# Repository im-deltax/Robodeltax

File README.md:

# Robodeltax

An educational AI chatbot robot under development by [im-deltax](https://github.com/im-deltax).

This repository currently publishes robot design assets: editable 3D files, printable parts, electronics designs, and garment patterns. The main chatbot application and production firmware are not available yet. Learning assistance is the intended application, not a capability demonstrated by this release.

## Current assets

| Folder | Contents |
| --- | --- |
| `Blender/` | Current assembled Kimono scene, V21 |
| `Vo_In_3D/` | Printable STL parts and available editable CAD/STEP sources |
| `Trang_Phuc/` | Current V20 garment patterns, sewing documents, print artwork and textures |
| `Dien_Tu/` | KiCad sources, custom libraries, prototype manufacturing exports and assembly documents |
| `Nguon_CAD_Giu_Lai/` | Older CAD retained for reference; not the current printing set |
| Other outfit folders | Design variants and reference-based studies, including folders marked `BANSAO` (copies); these are not all current approved manufacturing sets |

Read **[MO_FILE_NAY_TRUOC.txt](MO_FILE_NAY_TRUOC.txt)** first for the current version selection and assembly limitations. `rule.md` contains design notes for the current robot, not general dimensions for every design variant.

## Development and validation status

- Main AI chatbot software and robot firmware: under development, not included.
- Complete PCB, battery, servo and cable fit inside the enclosure: not confirmed.
- Electronics: prototype designs, not electrically validated on physical hardware.
- V21 updates the 1.9-inch display mounting; the proposed head rotation and 4.5 mm neck lift are not integrated.
- Native CAD coverage is partial: the current V21 FreeCAD/STEP set covers the head/display mount, not a complete newly rebuilt body CAD assembly.
- Garment patterns should be printed at 100% scale and their calibration marks checked before cutting.

Do not treat the presence of manufacturing exports as proof of a fully tested or production-ready robot. Follow the wiring and USB-mode notes in the original documents.

## Downloading large files

Large design assets use Git LFS. Install Git LFS, then run:

```sh
git lfs install
git clone https://github.com/im-deltax/Robodeltax.git
cd Robodeltax
git lfs pull
```

## Licensing and provenance

Copyright (C) 2026 Trần Minh Triết (im-deltax).

Unless a file or component states otherwise, original copyrightable material in this repository owned by Trần Minh Triết is licensed under the **GNU General Public License, version 3 only (GPL-3.0-only)**. See [LICENSE](LICENSE) for the complete terms. This includes the original design files and documentation to the extent the author owns the applicable copyright. This notice does not add chatbot software or firmware that has not yet been published.

Third-party components, libraries, artwork and reference-derived material retain their own licenses and rights; this notice does not relicense material the author does not own. Folder names such as `BANSAO` alone do not establish authorship or licensing. Provenance of reference-derived material remains to be documented.

GPL-3.0 permits commercial use. Obligations depend on how covered works are modified and conveyed; see the actual license rather than assuming every private modification must be published. Applying GPL to design files is not hardware certification, physical validation or a grant of third-party rights.

## Contributing

Please open an issue for questions, reproducibility reports, documentation corrections or proposed contributions. Include the file/version used and distinguish simulated results from physical tests. Do not post credentials or private user conversations.

---

## Tiếng Việt

Robodeltax là dự án robot chatbot AI hỗ trợ học tập đang phát triển. Bản công khai ban đầu gồm thiết kế vỏ, điện tử, cảnh Blender và rập trang phục; **chưa có source chatbot chính hoặc firmware hoàn chỉnh**. Đọc `MO_FILE_NAY_TRUOC.txt` để chọn đúng bộ hiện hành. Chưa xác nhận lắp vừa toàn bộ linh kiện hoặc kiểm thử điện thực tế. Phần tài nguyên gốc thuộc quyền sở hữu của Trần Minh Triết được cấp phép GPL-3.0-only, trừ khi có ghi chú khác. Thành phần bên thứ ba giữ giấy phép và quyền tương ứng, nguồn gốc tài nguyên tham khảo cần được ghi rõ.

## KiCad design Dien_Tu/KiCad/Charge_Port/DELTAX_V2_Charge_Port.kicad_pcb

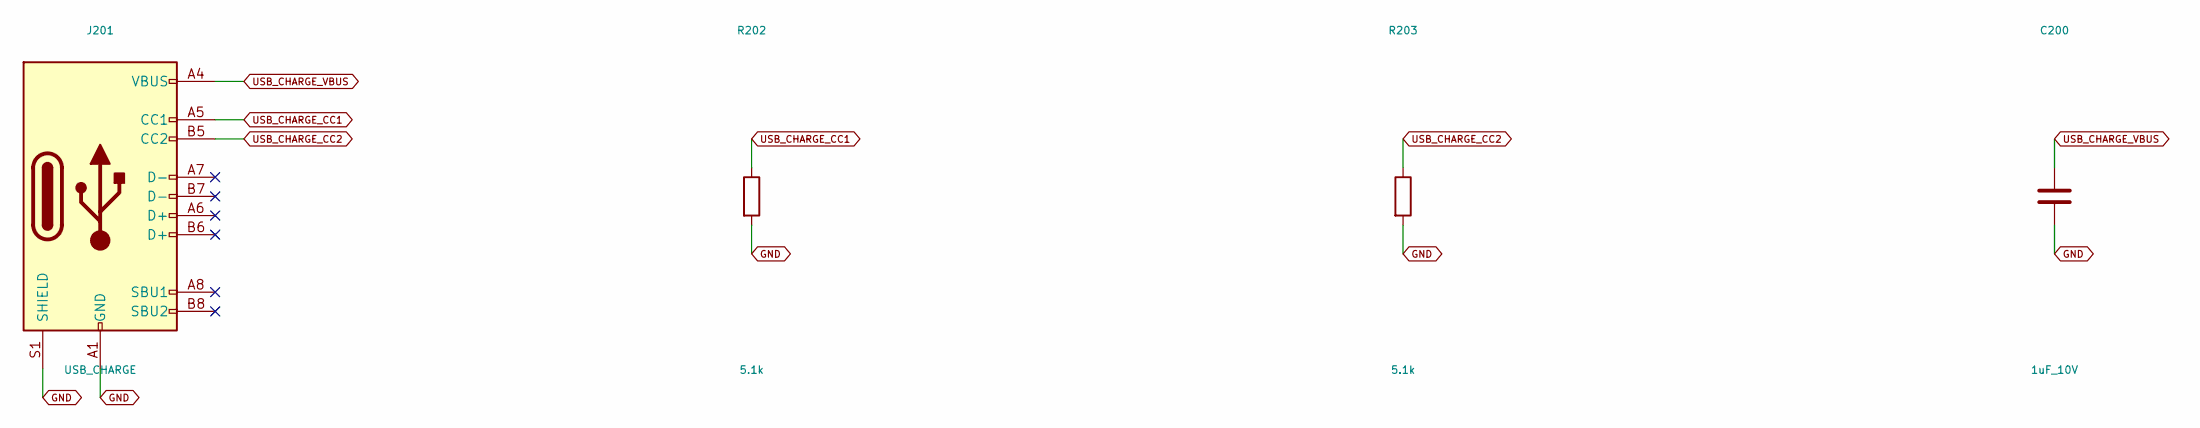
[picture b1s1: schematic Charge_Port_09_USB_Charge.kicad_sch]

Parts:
C200: 1uF_10V; C_0603_1608Metric
J201: USB_CHARGE; USB_C_Receptacle_GCT_USB4105-xx-A_16P_TopMnt_Horizontal
R202, R203: 5.1k; R_0603_1608Metric

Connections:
GND: C200.2, J201.A1 (GND), J201.A12 (GND), J201.B1 (GND), J201.B12 (GND), J201.S1 (SHIELD), R202.2, R203.2; also elsewhere on the board
USB_CHARGE_CC1: J201.A5 (CC1), R202.1
USB_CHARGE_CC2: J201.B5 (CC2), R203.1
USB_CHARGE_VBUS: C200.1, J201.A4 (VBUS), J201.A9 (VBUS), J201.B4 (VBUS), J201.B9 (VBUS); also elsewhere on the board

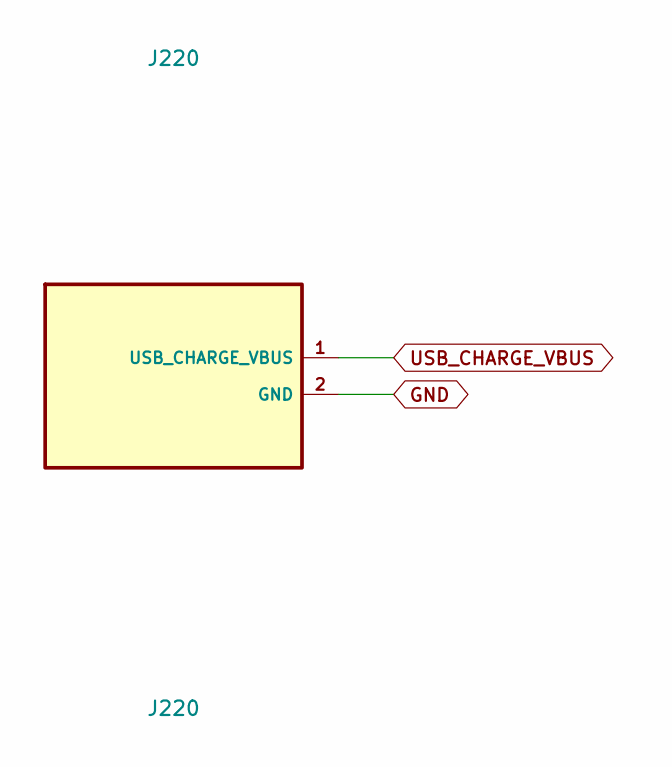
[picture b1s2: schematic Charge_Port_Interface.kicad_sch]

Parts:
J220: J220; PowerPads_2

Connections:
GND: J220.2 (GND); also elsewhere on the board
USB_CHARGE_VBUS: J220.1 (USB_CHARGE_VBUS); also elsewhere on the board

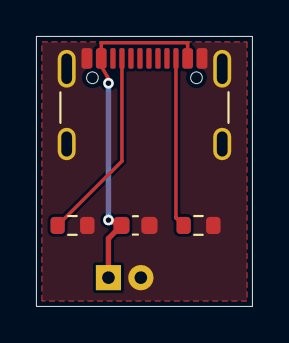
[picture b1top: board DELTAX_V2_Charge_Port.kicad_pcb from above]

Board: 2 copper layers, 12.0 x 15.0 mm, 5 parts (0 on the bottom side), 4 nets.

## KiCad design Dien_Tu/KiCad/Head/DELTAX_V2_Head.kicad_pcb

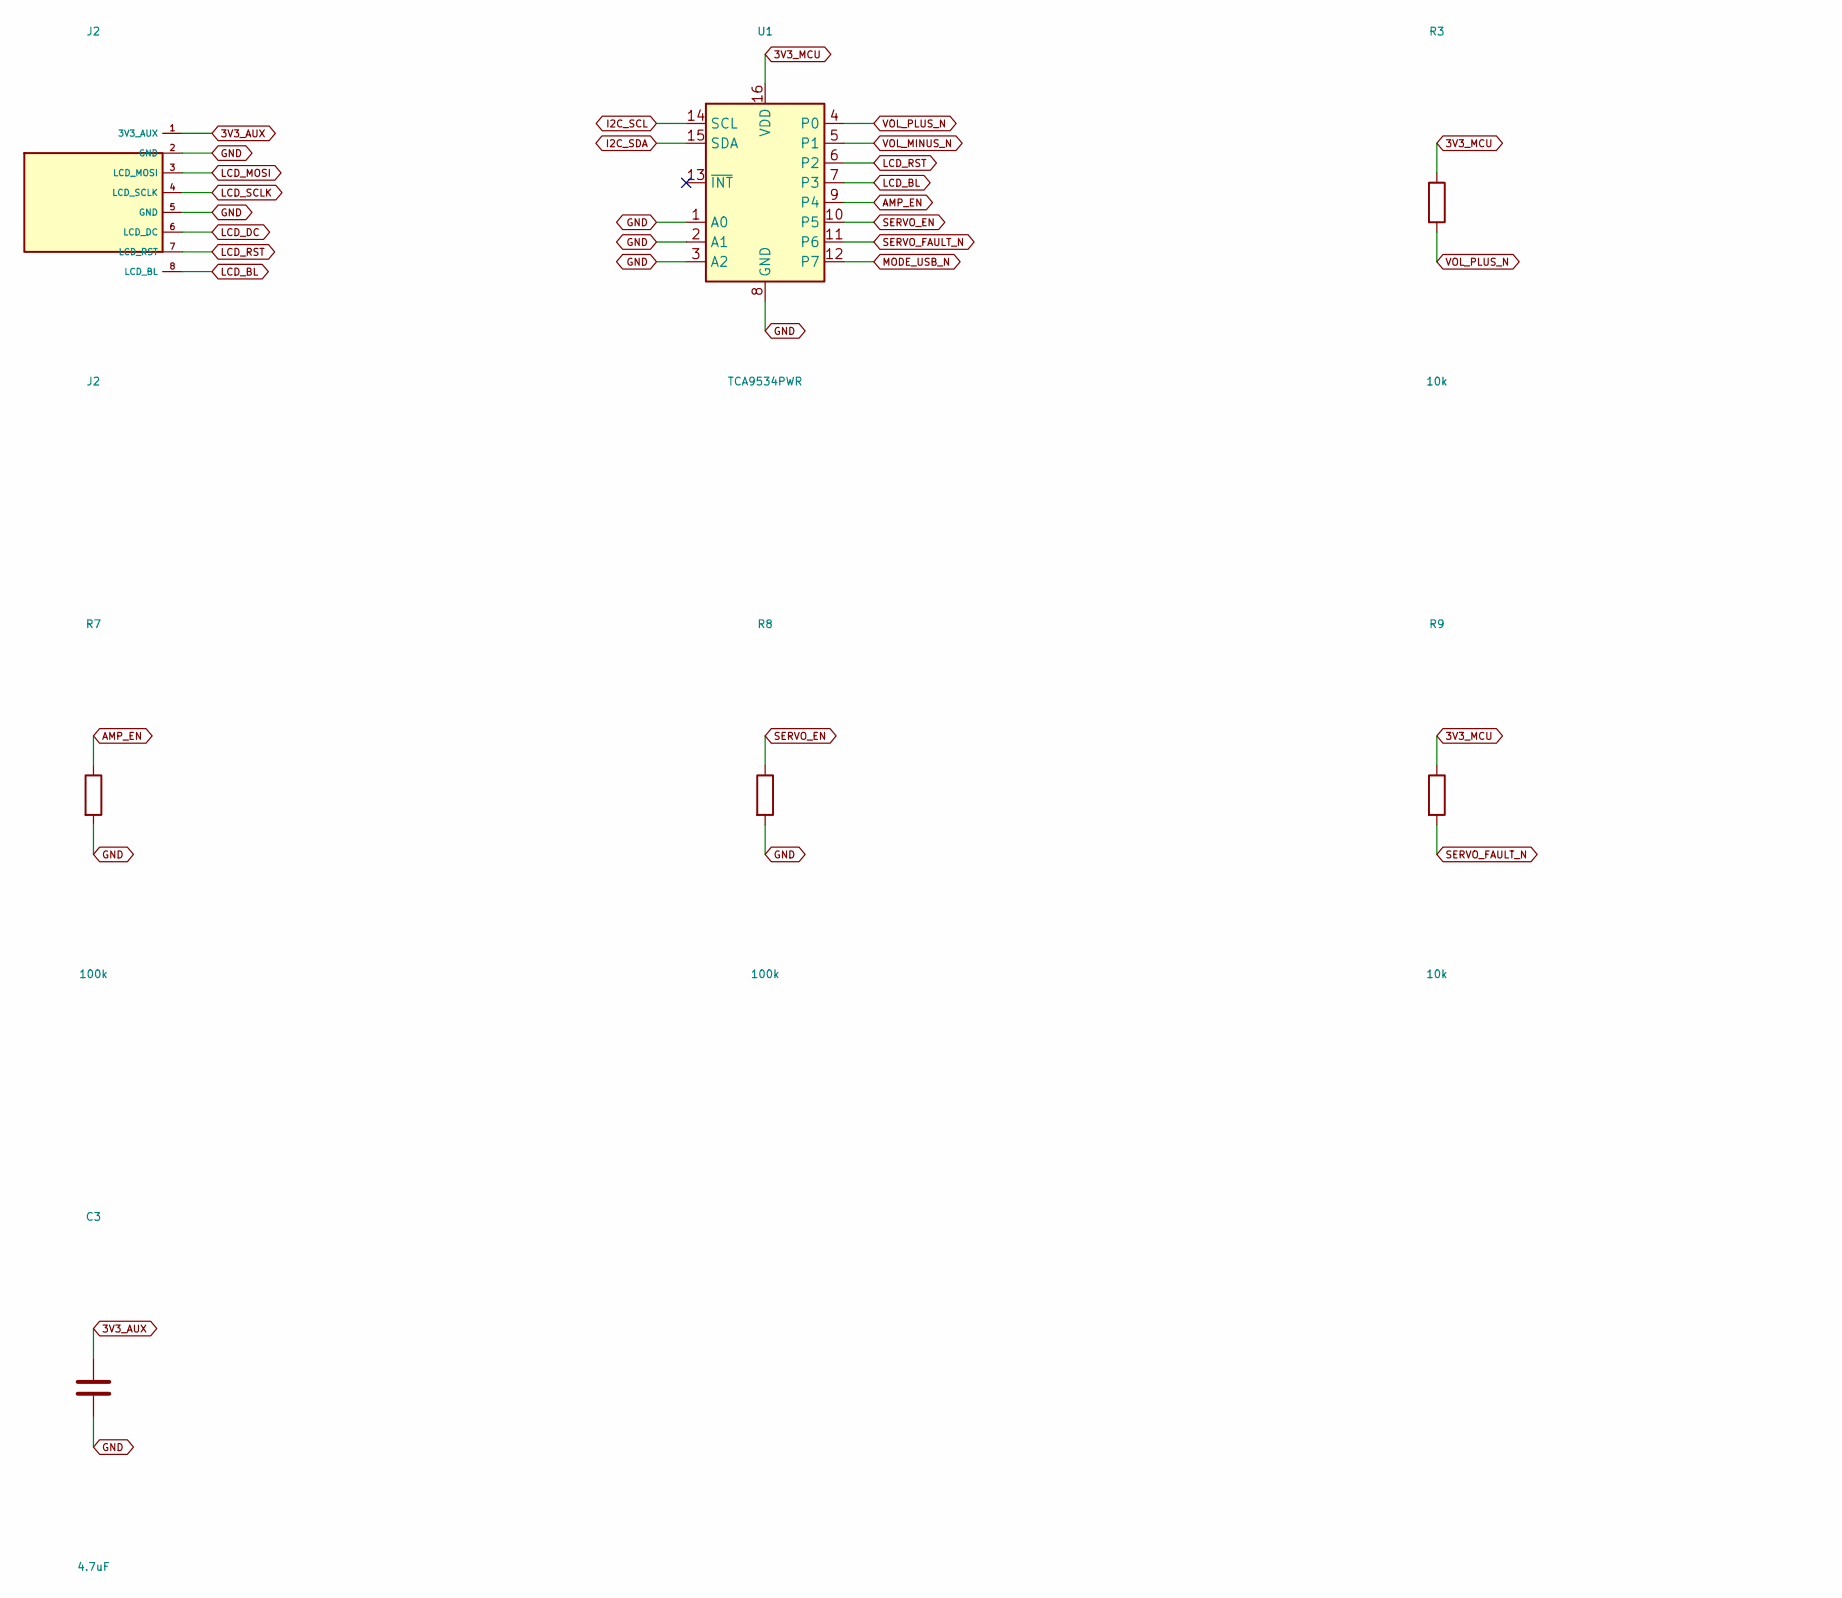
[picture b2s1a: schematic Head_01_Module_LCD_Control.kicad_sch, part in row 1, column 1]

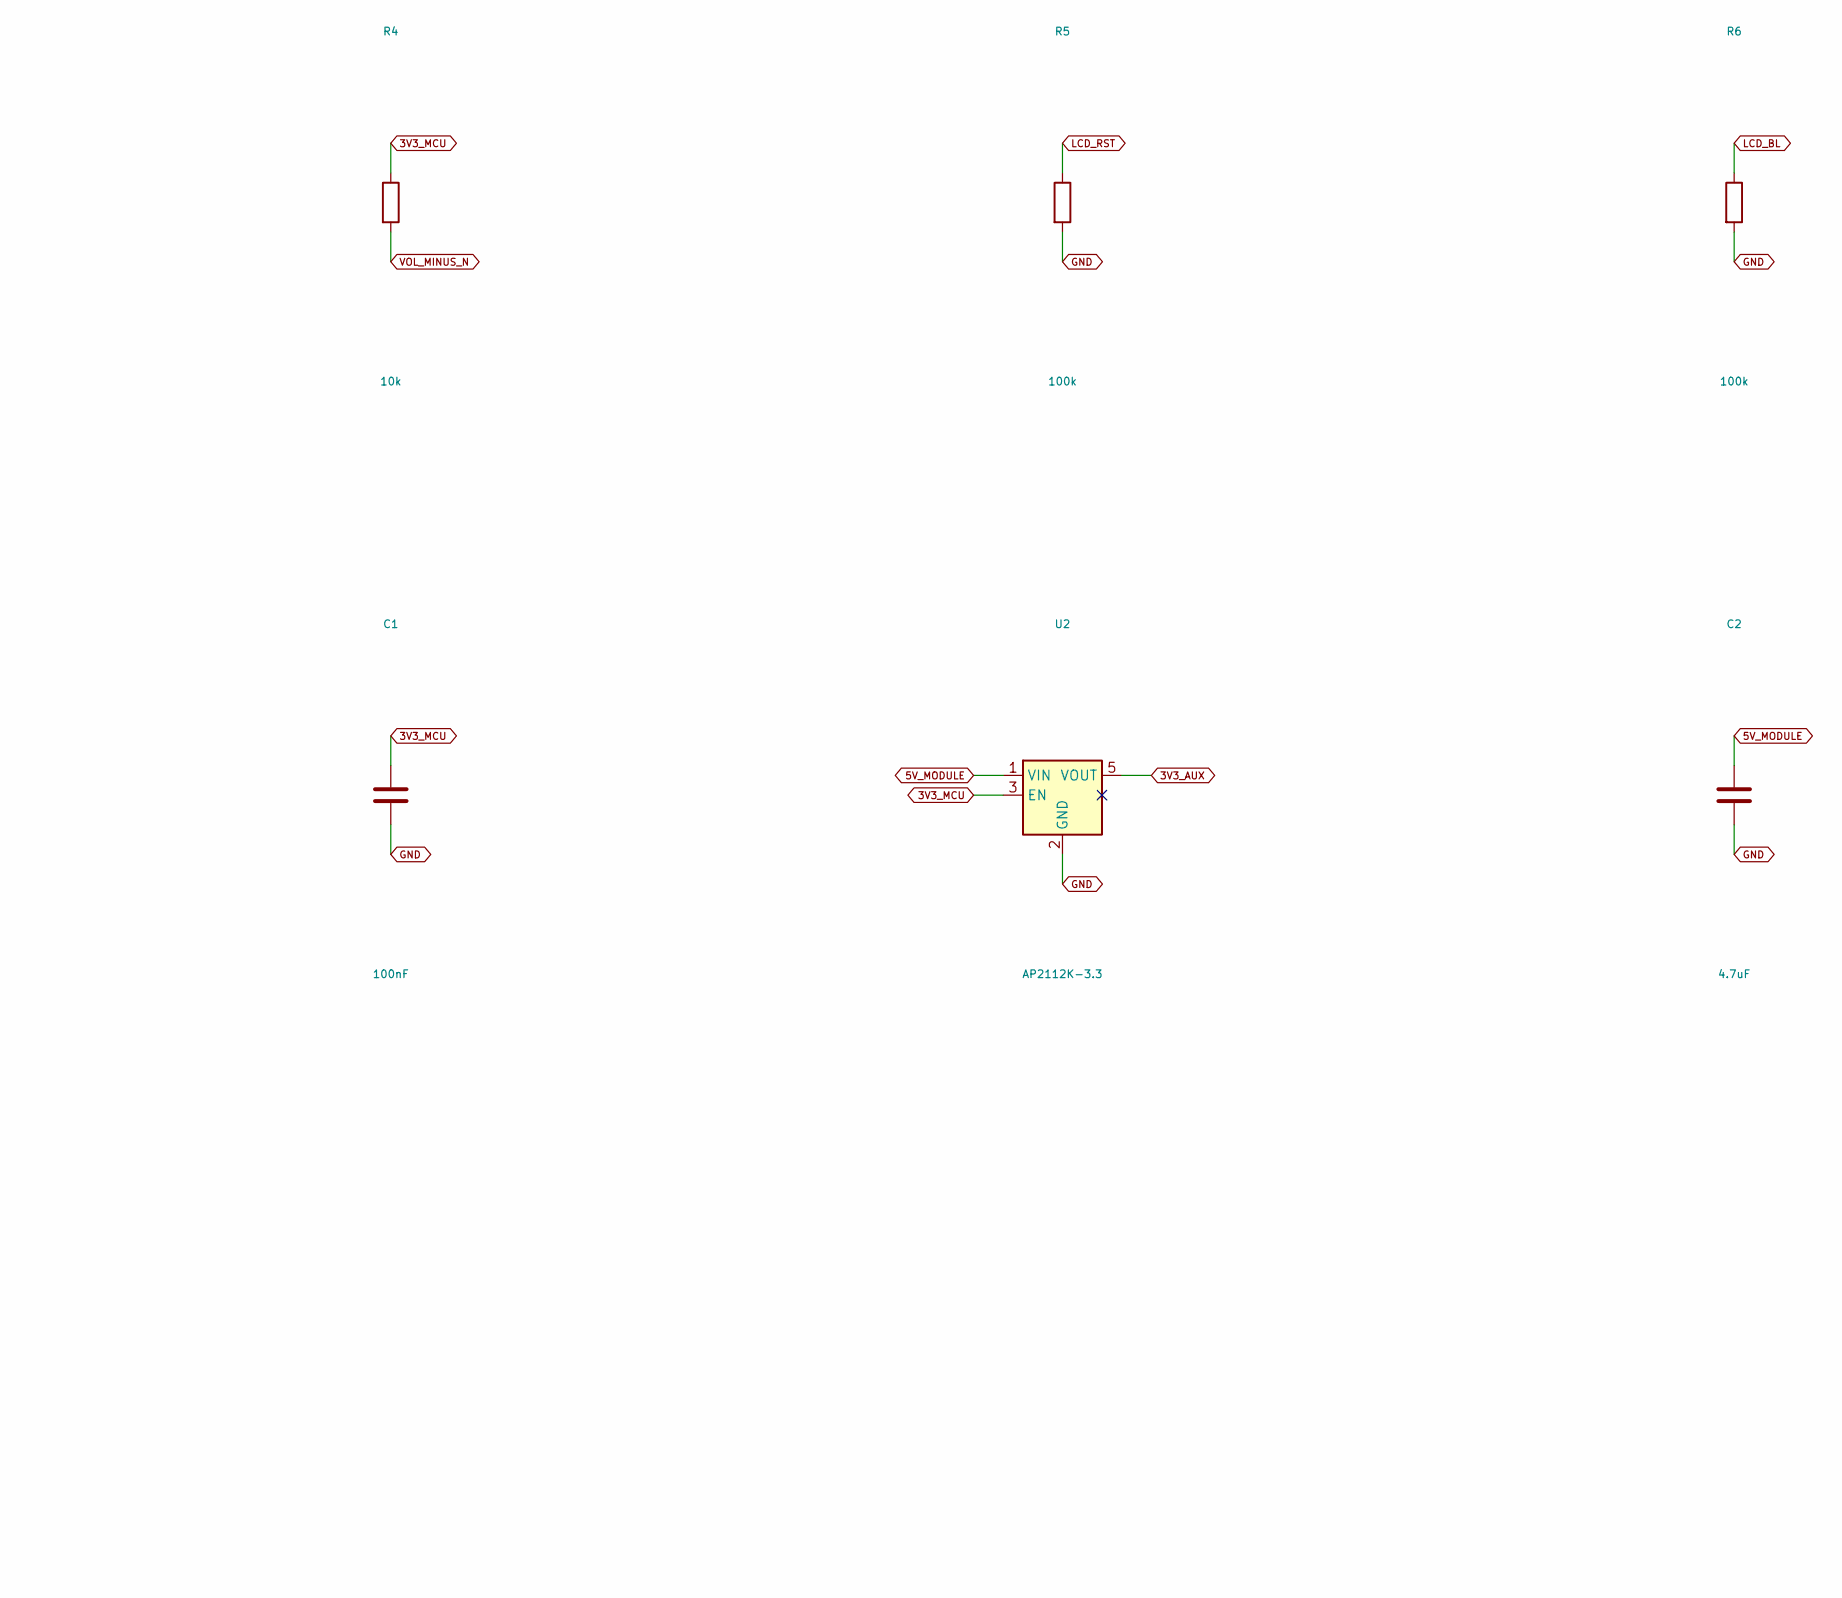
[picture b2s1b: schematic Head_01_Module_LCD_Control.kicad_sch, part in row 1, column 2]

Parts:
C1: 100nF; C_0603_1608Metric
C2, C3: 4.7uF; C_0603_1608Metric
J2: J2; JST_GH_SM08B-GHS-TB_1x08-1MP_P1.25mm_Horizontal
R3, R4, R9: 10k; R_0603_1608Metric
R5, R6, R7, R8: 100k; R_0603_1608Metric
U1: TCA9534PWR; TSSOP-16_4.4x5mm_P0.65mm
U2: AP2112K-3.3; SOT-23-5

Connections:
3V3_AUX: C3.1, J2.1 (3V3_AUX), U2.5 (VOUT)
3V3_MCU: C1.1, R3.1, R4.1, R9.1, U1.16 (VDD), U2.3 (EN); also elsewhere on the board
5V_MODULE: C2.1, U2.1 (VIN); also elsewhere on the board
AMP_EN: R7.1, U1.9 (P4); also elsewhere on the board
GND: C1.2, C2.2, C3.2, J2.2 (GND), J2.5 (GND), R5.2, R6.2, R7.2, R8.2, U1.1 (A0), U1.2 (A1), U1.3 (A2), U1.8 (GND), U2.2 (GND); also elsewhere on the board
I2C_SCL: U1.14 (SCL); also elsewhere on the board
I2C_SDA: U1.15 (SDA); also elsewhere on the board
LCD_BL: J2.8 (LCD_BL), R6.1, U1.7 (P3)
LCD_DC: J2.6 (LCD_DC); also elsewhere on the board
LCD_MOSI: J2.3 (LCD_MOSI); also elsewhere on the board
LCD_RST: J2.7 (LCD_RST), R5.1, U1.6 (P2)
LCD_SCLK: J2.4 (LCD_SCLK); also elsewhere on the board
MODE_USB_N: U1.12 (P7); also elsewhere on the board
SERVO_EN: R8.1, U1.10 (P5); also elsewhere on the board
SERVO_FAULT_N: R9.2, U1.11 (P6); also elsewhere on the board
VOL_MINUS_N: R4.2, U1.5 (P1); also elsewhere on the board
VOL_PLUS_N: R3.2, U1.4 (P0); also elsewhere on the board

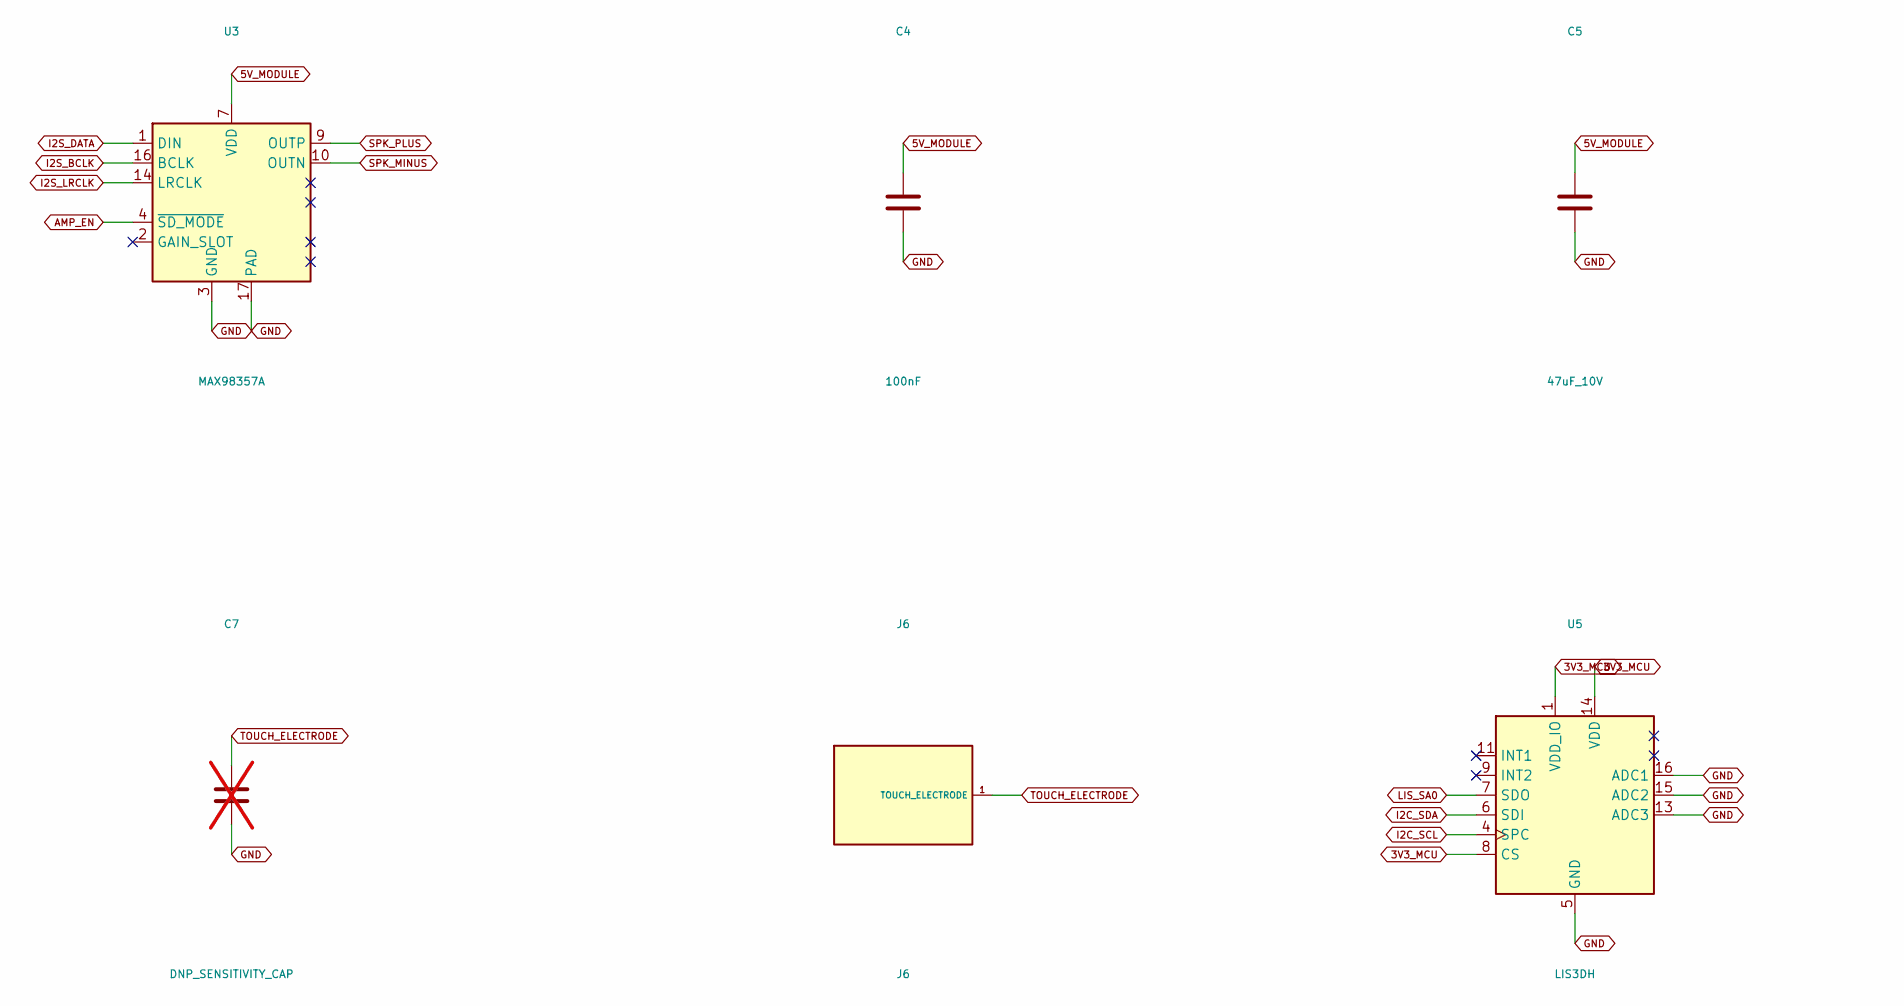
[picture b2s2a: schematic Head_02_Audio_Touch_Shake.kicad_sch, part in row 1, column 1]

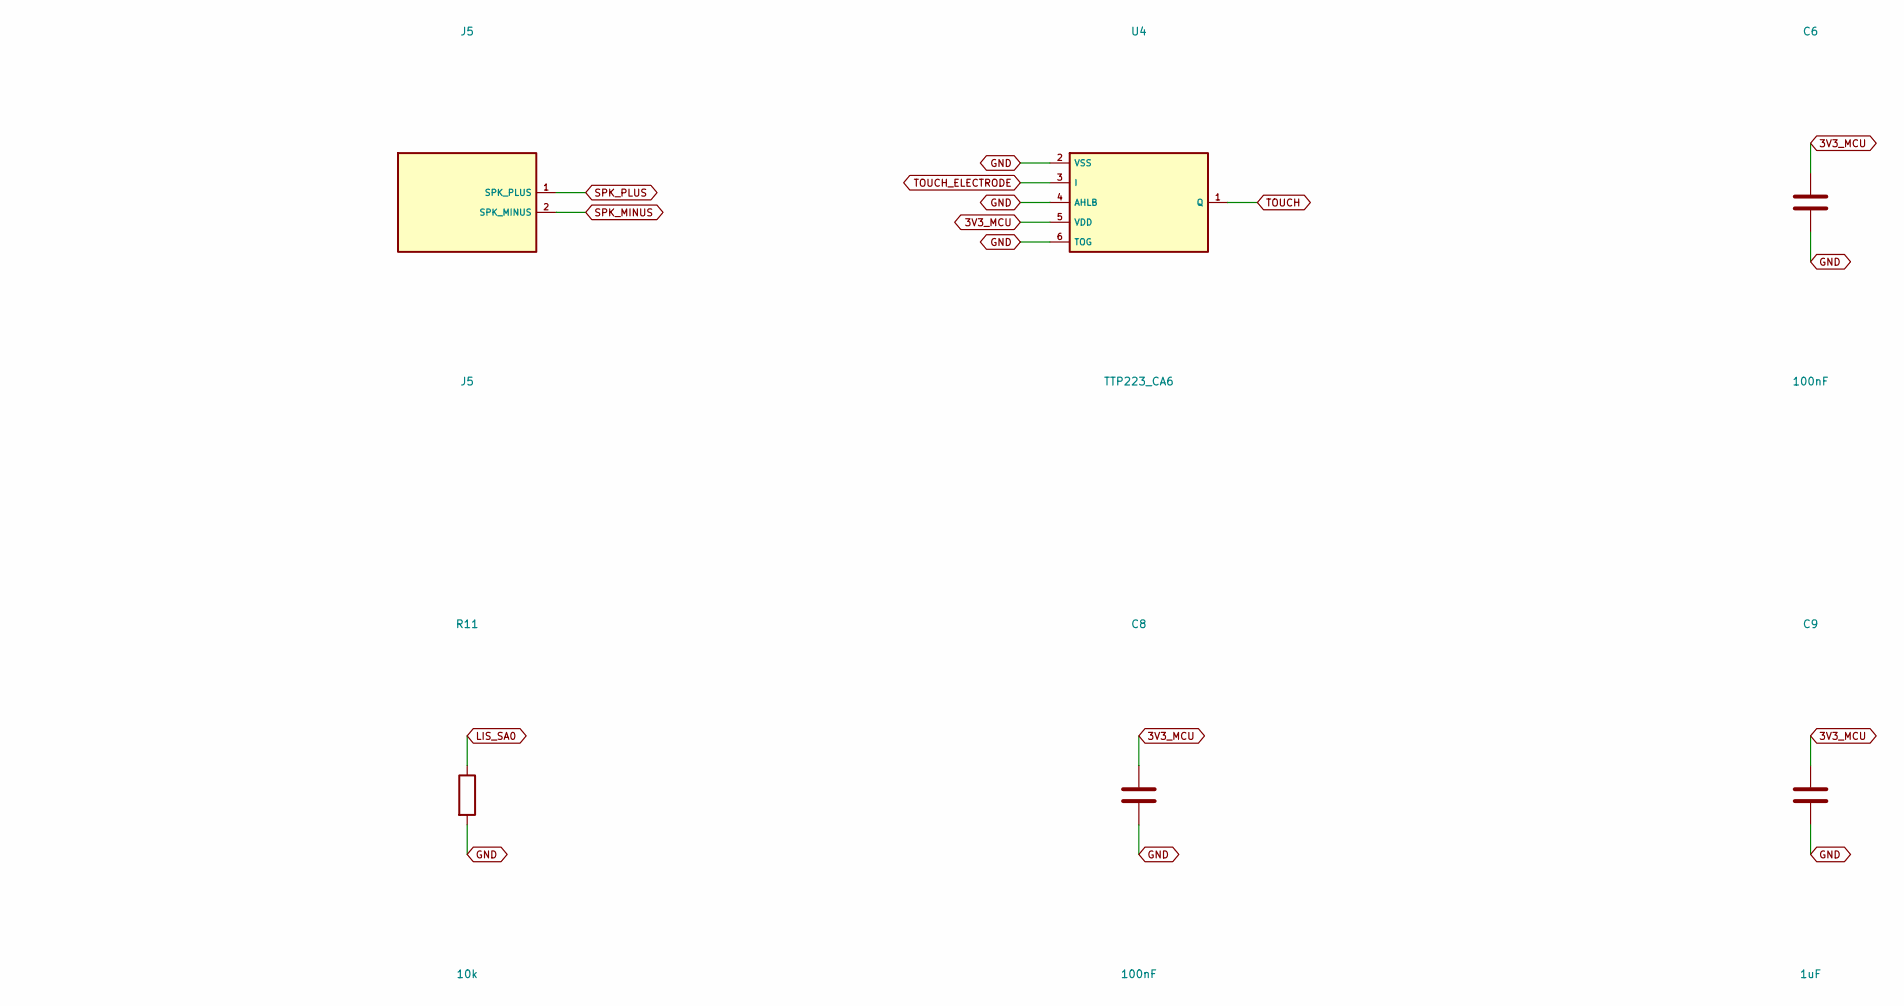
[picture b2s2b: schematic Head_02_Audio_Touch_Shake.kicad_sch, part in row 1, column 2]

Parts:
C4: 100nF; C_0402_1005Metric
C5: 47uF_10V; C_0805_2012Metric
C6, C8: 100nF; C_0603_1608Metric
C7: DNP_SENSITIVITY_CAP; C_0603_1608Metric; not fitted
C9: 1uF; C_0603_1608Metric
J5: J5; WirePads_2
J6: J6; WirePads_1
R11: 10k; R_0603_1608Metric
U3: MAX98357A; TQFN-16-1EP_3x3mm_P0.5mm_EP1.23x1.23mm
U4: TTP223_CA6; SOT-23-6
U5: LIS3DH; LGA-16_3x3mm_P0.5mm_LayoutBorder3x5y

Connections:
3V3_MCU: C6.1, C8.1, C9.1, U4.5 (VDD), U5.1 (VDD_IO), U5.8 (CS), U5.14 (VDD); also elsewhere on the board
5V_MODULE: C4.1, C5.1, U3.7 (VDD), U3.8 (VDD); also elsewhere on the board
AMP_EN: U3.4 (~SD_MODE); also elsewhere on the board
GND: C4.2, C5.2, C6.2, C7.2, C8.2, C9.2, R11.2, U3.3 (GND), U3.11 (GND), U3.15 (GND), U3.17 (PAD), U4.2 (VSS), U4.4 (AHLB), U4.6 (TOG), U5.5 (GND), U5.10 (GND), U5.12 (GND), U5.13 (ADC3), U5.15 (ADC2), U5.16 (ADC1); also elsewhere on the board
I2C_SCL: U5.4 (SPC); also elsewhere on the board
I2C_SDA: U5.6 (SDI); also elsewhere on the board
I2S_BCLK: U3.16 (BCLK); also elsewhere on the board
I2S_DATA: U3.1 (DIN); also elsewhere on the board
I2S_LRCLK: U3.14 (LRCLK); also elsewhere on the board
LIS_SA0: R11.1, U5.7 (SDO)
SPK_MINUS: J5.2 (SPK_MINUS), U3.10 (OUTN)
SPK_PLUS: J5.1 (SPK_PLUS), U3.9 (OUTP)
TOUCH: U4.1 (Q); also elsewhere on the board
TOUCH_ELECTRODE: C7.1, J6.1, U4.3 (I)

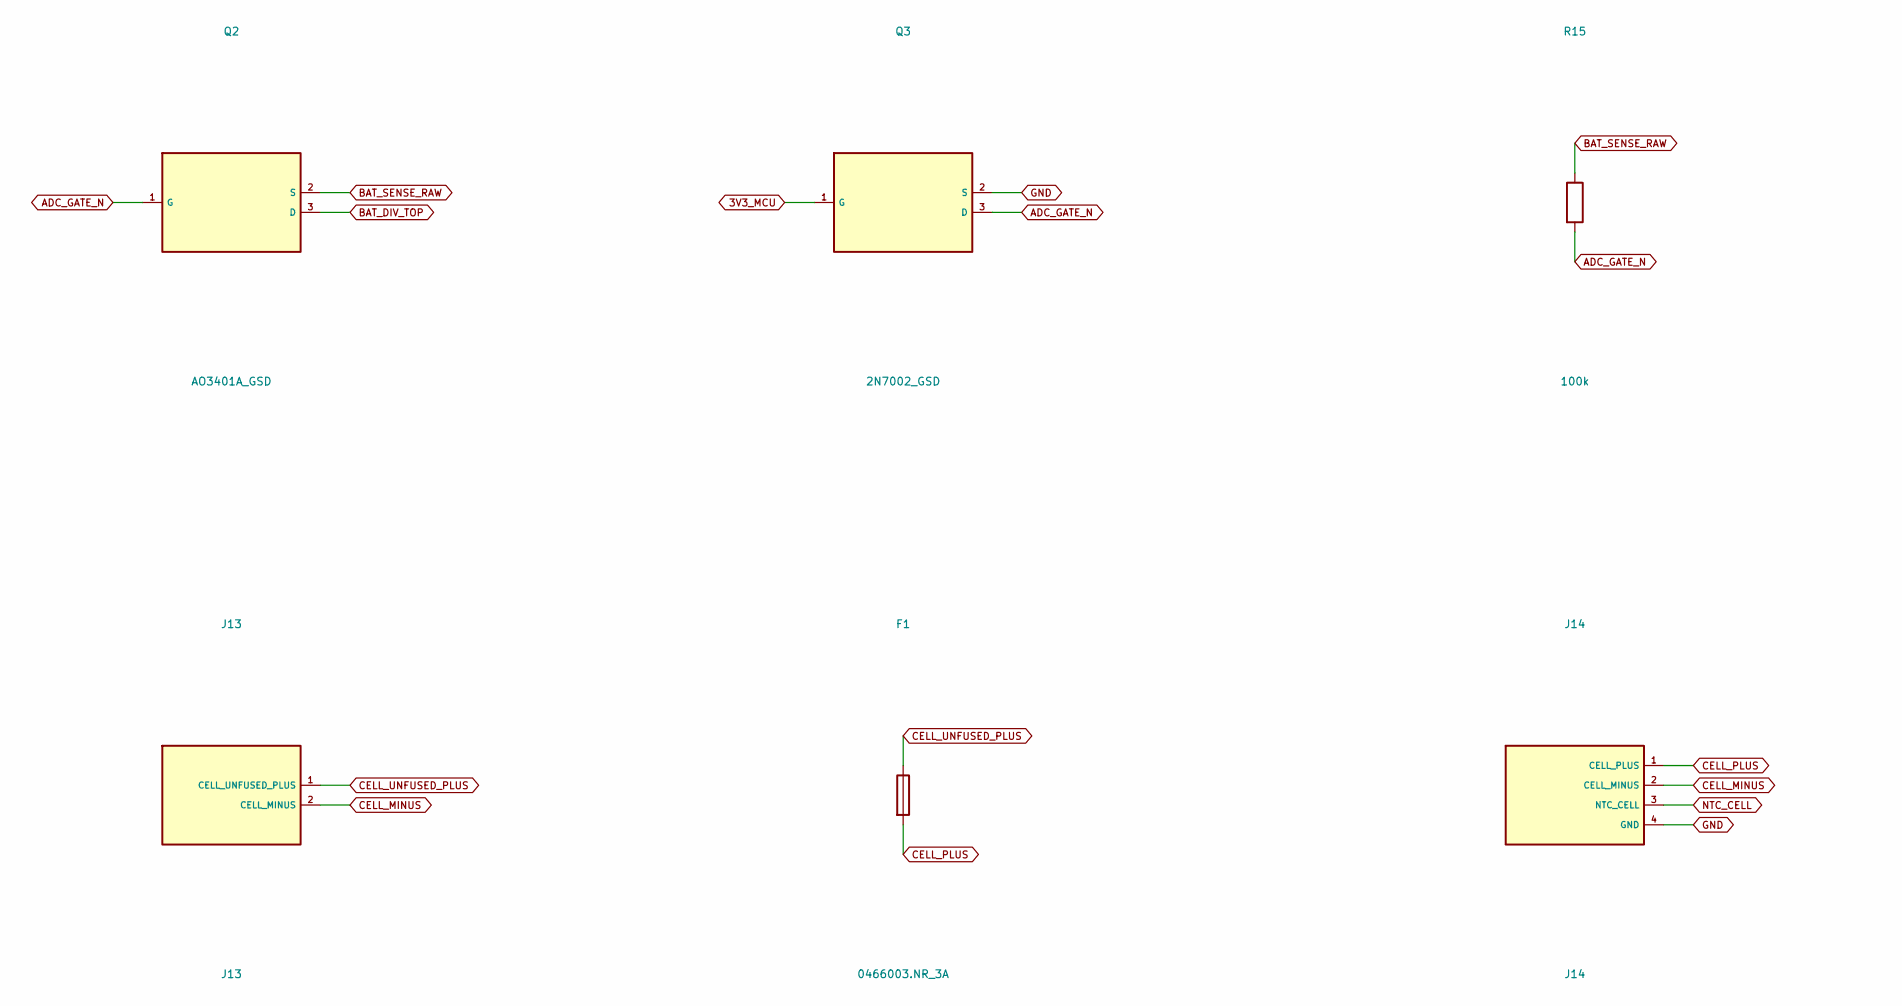
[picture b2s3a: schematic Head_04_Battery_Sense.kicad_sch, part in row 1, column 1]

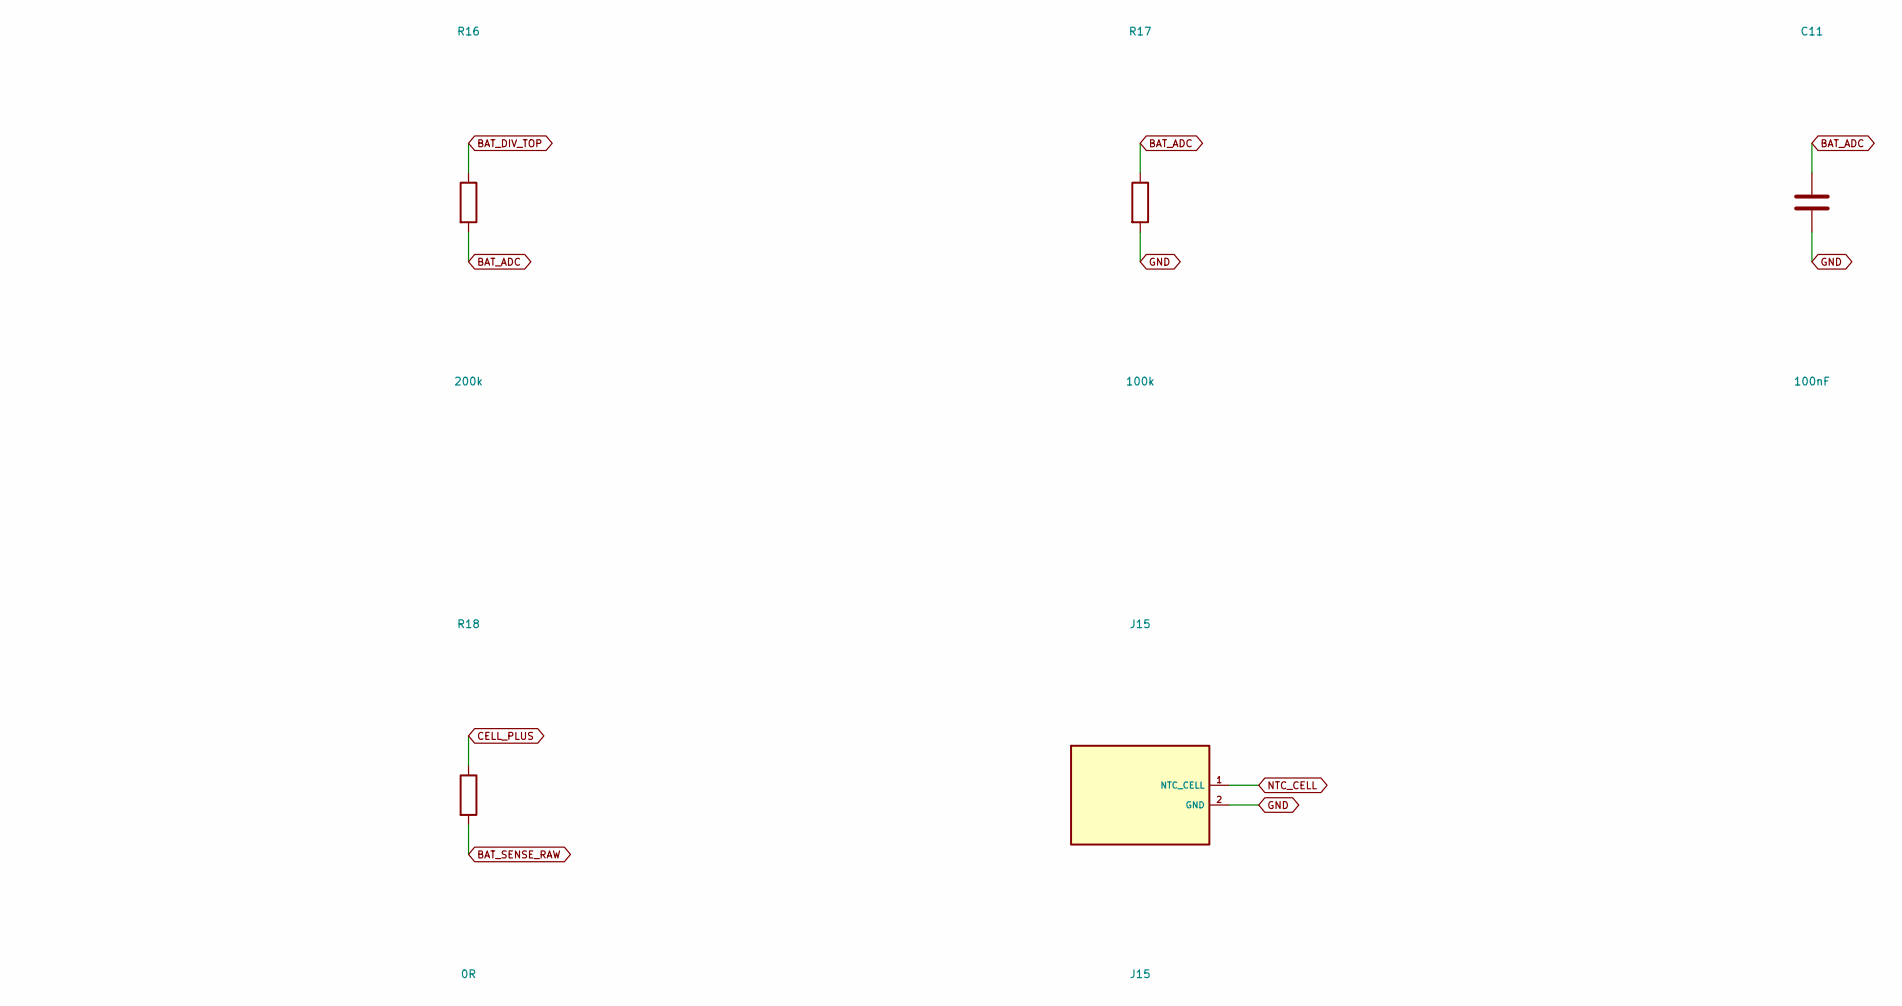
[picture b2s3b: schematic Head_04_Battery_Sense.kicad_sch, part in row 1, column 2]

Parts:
C11: 100nF; C_0603_1608Metric
F1: 0466003.NR_3A; Fuse_1206_3216Metric
J13: J13; PowerPads_2
J14: J14; PowerPads_4
J15: J15; WirePads_2
Q2: AO3401A_GSD; SOT-23
Q3: 2N7002_GSD; SOT-23
R15, R17: 100k; R_0603_1608Metric
R16: 200k; R_0603_1608Metric
R18: 0R; R_0603_1608Metric

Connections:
3V3_MCU: Q3.1 (G); also elsewhere on the board
ADC_GATE_N: Q2.1 (G), Q3.3 (D), R15.2
BAT_ADC: C11.1, R16.2, R17.1; also elsewhere on the board
BAT_DIV_TOP: Q2.3 (D), R16.1
BAT_SENSE_RAW: Q2.2 (S), R15.1, R18.2
CELL_MINUS: J13.2 (CELL_MINUS), J14.2 (CELL_MINUS)
CELL_PLUS: F1.2, J14.1 (CELL_PLUS), R18.1
CELL_UNFUSED_PLUS: F1.1, J13.1 (CELL_UNFUSED_PLUS)
GND: C11.2, J14.4 (GND), J15.2 (GND), Q3.2 (S), R17.2; also elsewhere on the board
NTC_CELL: J14.3 (NTC_CELL), J15.1 (NTC_CELL)

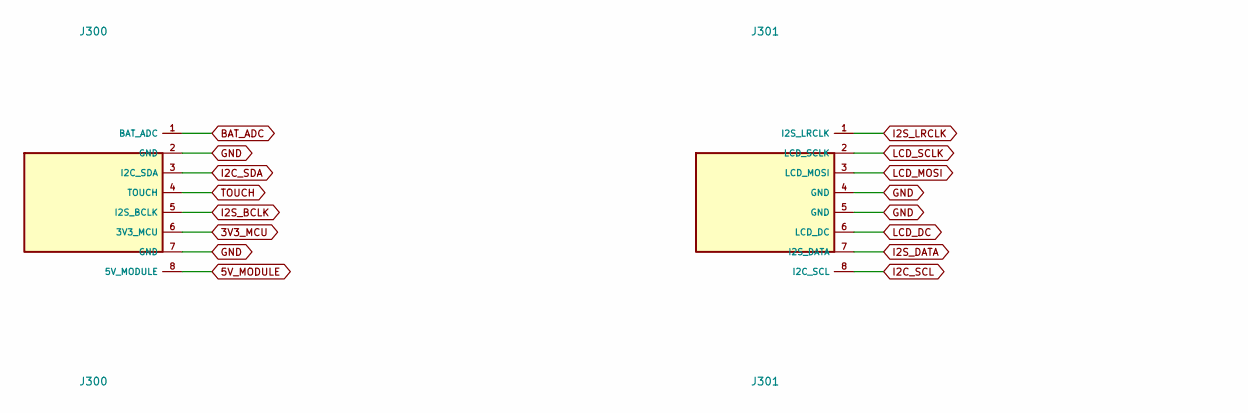
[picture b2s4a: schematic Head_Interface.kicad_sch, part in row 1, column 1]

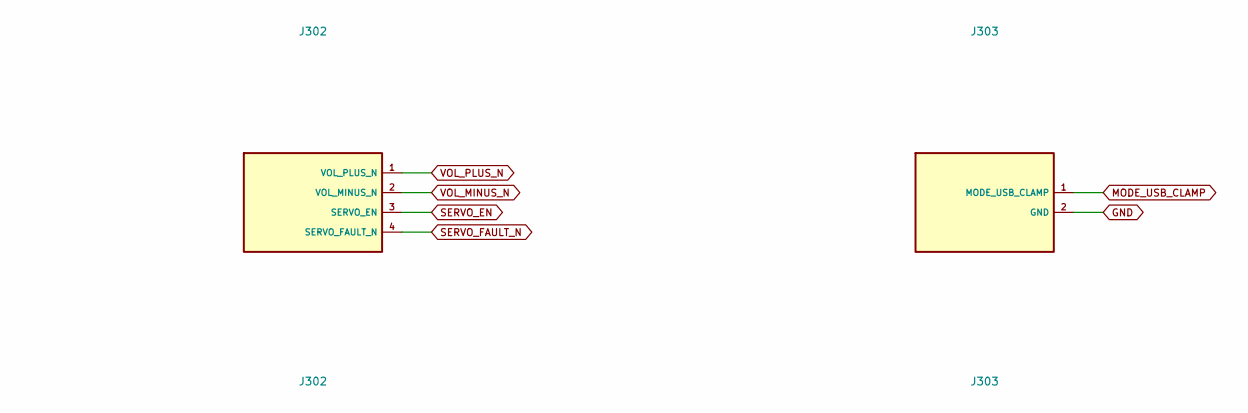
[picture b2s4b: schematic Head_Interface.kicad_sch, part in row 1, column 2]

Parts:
J300: J300; WirePads_8
J301: J301; WirePads_8
J302: J302; WirePads_4
J303: J303; WirePads_2

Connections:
3V3_MCU: J300.6 (3V3_MCU); also elsewhere on the board
5V_MODULE: J300.8 (5V_MODULE); also elsewhere on the board
BAT_ADC: J300.1 (BAT_ADC); also elsewhere on the board
GND: J300.2 (GND), J300.7 (GND), J301.4 (GND), J301.5 (GND), J303.2 (GND); also elsewhere on the board
I2C_SCL: J301.8 (I2C_SCL); also elsewhere on the board
I2C_SDA: J300.3 (I2C_SDA); also elsewhere on the board
I2S_BCLK: J300.5 (I2S_BCLK); also elsewhere on the board
I2S_DATA: J301.7 (I2S_DATA); also elsewhere on the board
I2S_LRCLK: J301.1 (I2S_LRCLK); also elsewhere on the board
LCD_DC: J301.6 (LCD_DC); also elsewhere on the board
LCD_MOSI: J301.3 (LCD_MOSI); also elsewhere on the board
LCD_SCLK: J301.2 (LCD_SCLK); also elsewhere on the board
MODE_USB_CLAMP: J303.1 (MODE_USB_CLAMP); also elsewhere on the board
SERVO_EN: J302.3 (SERVO_EN); also elsewhere on the board
SERVO_FAULT_N: J302.4 (SERVO_FAULT_N); also elsewhere on the board
TOUCH: J300.4 (TOUCH); also elsewhere on the board
VOL_MINUS_N: J302.2 (VOL_MINUS_N); also elsewhere on the board
VOL_PLUS_N: J302.1 (VOL_PLUS_N); also elsewhere on the board

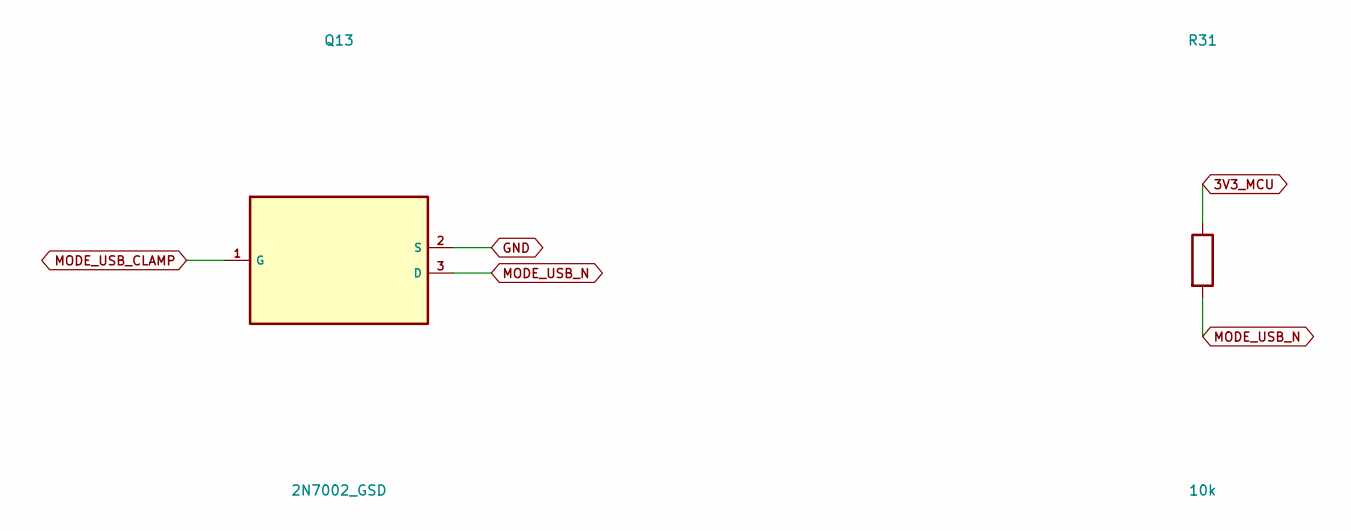
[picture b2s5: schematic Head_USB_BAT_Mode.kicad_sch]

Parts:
Q13: 2N7002_GSD; SOT-23
R31: 10k; R_0603_1608Metric

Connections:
3V3_MCU: R31.1; also elsewhere on the board
GND: Q13.2 (S); also elsewhere on the board
MODE_USB_CLAMP: Q13.1 (G); also elsewhere on the board
MODE_USB_N: Q13.3 (D), R31.2; also elsewhere on the board

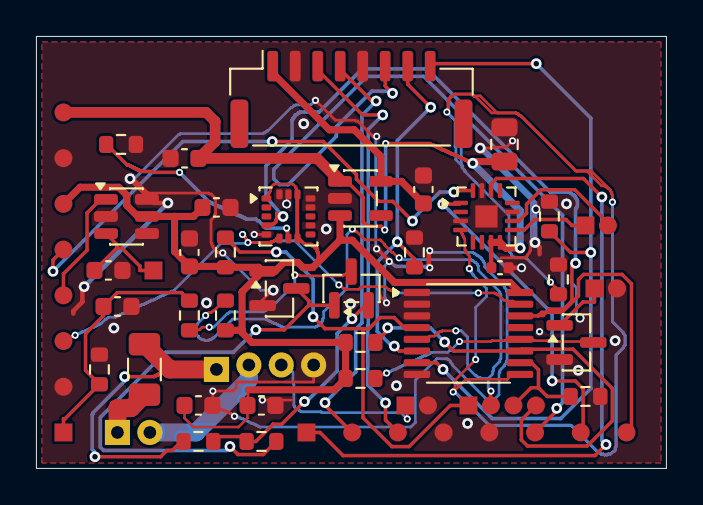
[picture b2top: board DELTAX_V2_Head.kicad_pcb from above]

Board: 2 copper layers, 35.0 x 24.0 mm, 42 parts (0 on the bottom side), 34 nets.
